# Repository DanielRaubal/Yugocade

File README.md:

<h1 align="center">YugoCade</h1>
<p align="center">Version 0.01</p>

<p align="center">

<p align="center">
Custom handheld arcade system running on Raspberry Pi Pico 2040 MCU, has multiple games on it such as YugoRun, Submarine, Cards, Slot.
</p>

</p>

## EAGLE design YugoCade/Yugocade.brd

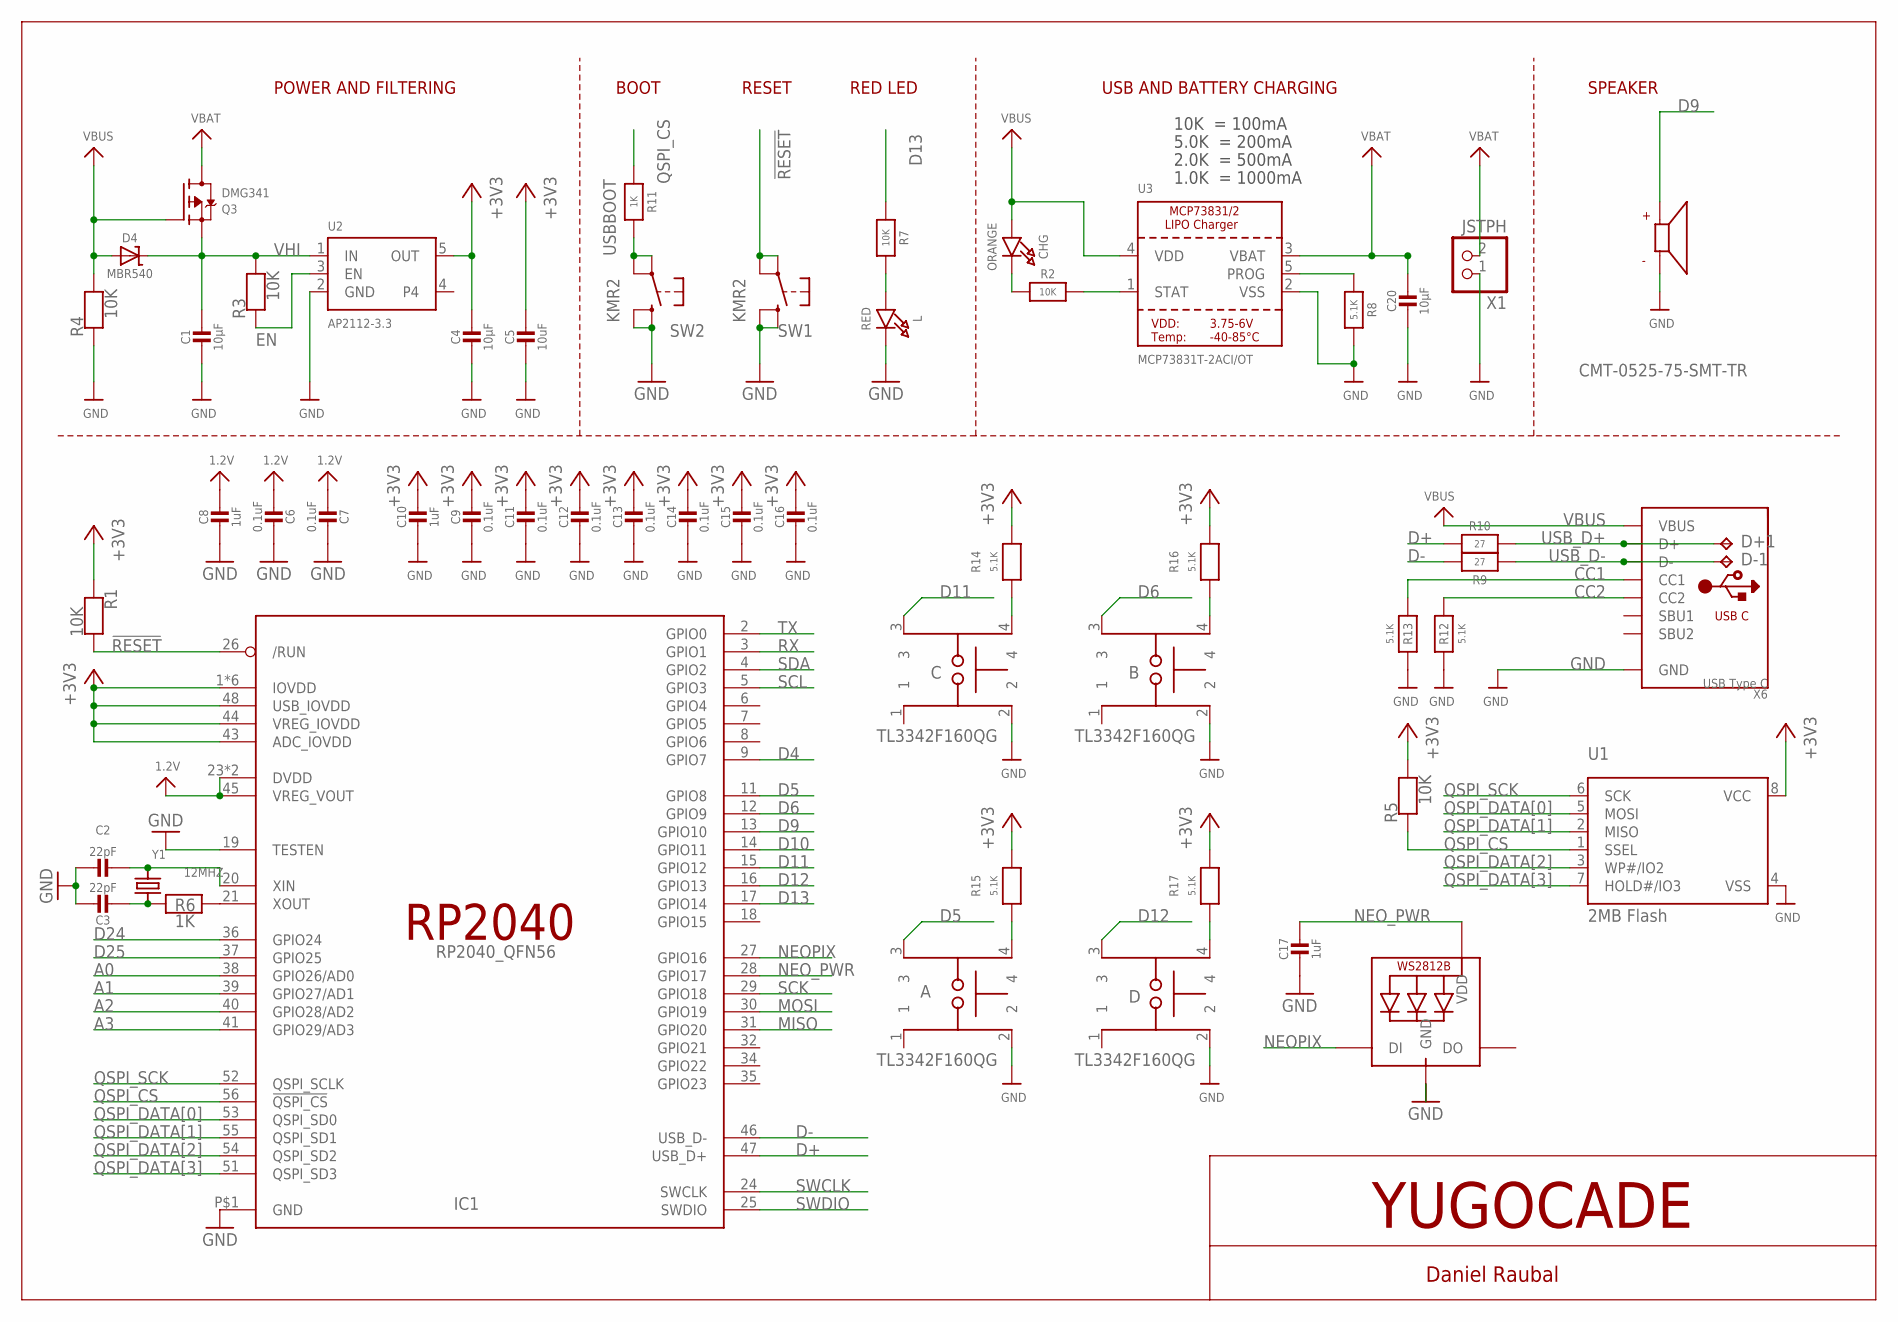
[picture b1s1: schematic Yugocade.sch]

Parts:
A: TL3342F160QG; SW_TL3342F160QG
B: TL3342F160QG; SW_TL3342F160QG
C: TL3342F160QG; SW_TL3342F160QG
C1, C4, C20: 10µF; 0805-NO
C2, C3: 22pF; 0603-NO
C5: 10uF; 0805-NO
C6, C7, C9, C11, C12, C13, C14, C15, C16: 0.1uF; 0603-NO
C8, C10, C17: 1uF; 0603-NO
CHG: ORANGE; CHIPLED_0603_NOOUTLINE
D: TL3342F160QG; SW_TL3342F160QG
D4: MBR540; SOD-123
D+1: TPB1,27; B1,27
D-1: TPB1,27; B1,27
IC1: RP2040_QFN56; QFN56_7MM_REDUCEDEPAD
L: RED; CHIPLED_0603_NOOUTLINE
LED1: WS2812B3535; LED3535
LS1: CMT-0525-75-SMT-TR; XDCR_CMT-0525-75-SMT-TR
Q3: DMG341; SOT23-R
R1, R2, R3, R4, R5, R7: 10K; 0603-NO
R6, R11: 1K; 0603-NO
R8, R12, R13, R14, R15, R16, R17: 5.1K; 0603-NO
R9, R10: 27; 0603-NO
SW1, SW2: KMR2; BTN_KMR2_4.6X2.8
U1: 2MB Flash; SOIC8_208MIL
U2: AP2112-3.3; SOT23-5@1
U3: MCP73831T-2ACI/OT; SOT23-5
X1: JSTPH; JSTPH2_BATT
X6: USB Type C; USB_C_CUSB31-CFM2AX-01-X
Y1: 12MHZ; CRYSTAL_2.5X2

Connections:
1.2V: C6.2, C7.2, C8.1, IC1.23 (DVDD), IC1.45 (VREG_VOUT), IC1.50 (DVDD)
!RESET: IC1.26 (/RUN), R1.2, SW1.A, SW1.A' (P1)
+3V3: C4.1, C5.1, C9.1, C10.1, C11.1, C12.1, C13.1, C14.1, C15.1, C16.1, IC1.1 (IOVDD), IC1.10 (IOVDD), IC1.22 (IOVDD), IC1.33 (IOVDD), IC1.42 (IOVDD), IC1.43 (ADC_IOVDD), IC1.44 (VREG_IOVDD), IC1.48 (USB_IOVDD), IC1.49 (IOVDD), R1.1, R5.2, R14.1, R15.1, R16.1, R17.1, U1.8 (VCC), U2.5 (OUT)
A0: IC1.38 (GPIO26/AD0)
A1: IC1.39 (GPIO27/AD1)
A2: IC1.40 (GPIO28/AD2)
A3: IC1.41 (GPIO29/AD3)
CC1: R13.2, X6.A5 (CC1)
CC2: R12.2, X6.B5 (CC2)
D4: IC1.9 (GPIO7)
D5: A.3, IC1.11 (GPIO8)
D6: B.3, IC1.12 (GPIO9)
D9: IC1.13 (GPIO10), LS1.P
D10: IC1.14 (GPIO11)
D11: C.3, IC1.15 (GPIO12)
D12: D.3, IC1.16 (GPIO13)
D13: IC1.17 (GPIO14), R7.1
D24: IC1.36 (GPIO24)
D25: IC1.37 (GPIO25)
D+: IC1.47 (USB_D+), R10.2
D-: IC1.46 (USB_D-), R9.2
EN: R3.1, U2.3 (EN)
GND: A.2, B.2, C.2, C1.2, C2.1, C3.1, C4.2, C5.2, C6.1, C7.1, C8.2, C9.2, C10.2, C11.2, C12.2, C13.2, C14.2, C15.2, C16.2, C17.2, C20.2, D.2, IC1.19 (TESTEN), IC1.P$1 (GND), L.C, LED1.4 (GND), LS1.N, R4.1, R8.2, R12.1, R13.1, SW1.B (S), SW1.B' (S1), SW2.B (S), SW2.B' (S1), U1.4 (VSS), U2.2 (GND), U3.2 (VSS), X1.1, X6.A1B12 (GND), X6.B1A12 (GND)
MISO: IC1.31 (GPIO20)
MOSI: IC1.30 (GPIO19)
unnamed: CHG.C, R2.1
unnamed: L.A, R7.2
unnamed: R2.2, U3.1 (STAT)
unnamed: R8.1, U3.5 (PROG)
unnamed: C2.2, IC1.20 (XIN), Y1.3 (2)
unnamed: C3.2, R6.1, Y1.1
unnamed: IC1.21 (XOUT), R6.2
unnamed: C.4, R14.2
unnamed: A.4, R15.2
unnamed: B.4, R16.2
unnamed: D.4, R17.2
NEOPIX: IC1.27 (GPIO16), LED1.1 (DI)
NEO_PWR: C17.1, IC1.28 (GPIO17), LED1.2 (VDD)
QSPI_CS: IC1.56 (!QSPI_CS), R5.1, R11.1, U1.1 (SSEL)
QSPI_DATA[0]: IC1.53 (QSPI_SD0), U1.5 (MOSI)
QSPI_DATA[1]: IC1.55 (QSPI_SD1), U1.2 (MISO)
QSPI_DATA[2]: IC1.54 (QSPI_SD2), U1.3 (WP#/IO2)
QSPI_DATA[3]: IC1.51 (QSPI_SD3), U1.7 (HOLD#/IO3)
QSPI_SCK: IC1.52 (QSPI_SCLK), U1.6 (SCK)
RX: IC1.3 (GPIO1)
SCK: IC1.29 (GPIO18)
SCL: IC1.5 (GPIO3)
SDA: IC1.4 (GPIO2)
SWCLK: IC1.24 (SWCLK)
SWDIO: IC1.25 (SWDIO)
TX: IC1.2 (GPIO0)
USBBOOT: R11.2, SW2.A, SW2.A' (P1)
USB_D+: D+1.TP, R10.1, X6.A6 (D+), X6.B6 (D+)
USB_D-: D-1.TP, R9.1, X6.A7 (D-), X6.B7 (D-)
VBAT: C20.1, Q3.3 (D), U3.3 (VBAT), X1.2
VBUS: CHG.A, D4.A, Q3.1 (G), R4.2, U3.4 (VDD), X6.A4B9 (VBUS), X6.B4A9 (VBUS)
VHI: C1.1, D4.C, Q3.2 (S), R3.2, U2.1 (IN)

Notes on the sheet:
POWER AND FILTERING
RESET
10K = 100mA
5.0K = 200mA
2.0K = 500mA
1.0K = 1000mA
USB AND BATTERY CHARGING
RED LED
YUGOCADE
Daniel Raubal
BOOT
SPEAKER

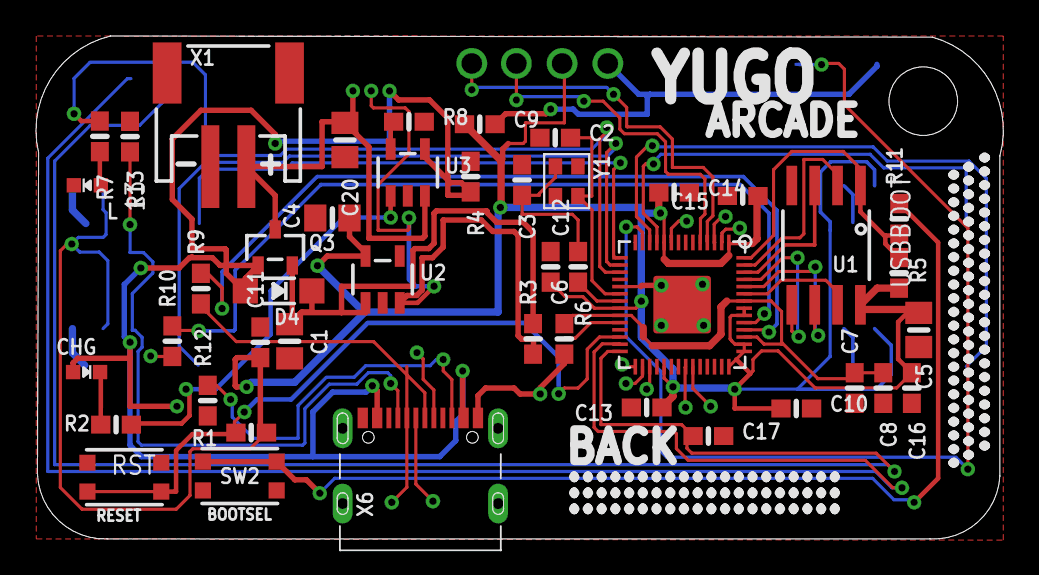
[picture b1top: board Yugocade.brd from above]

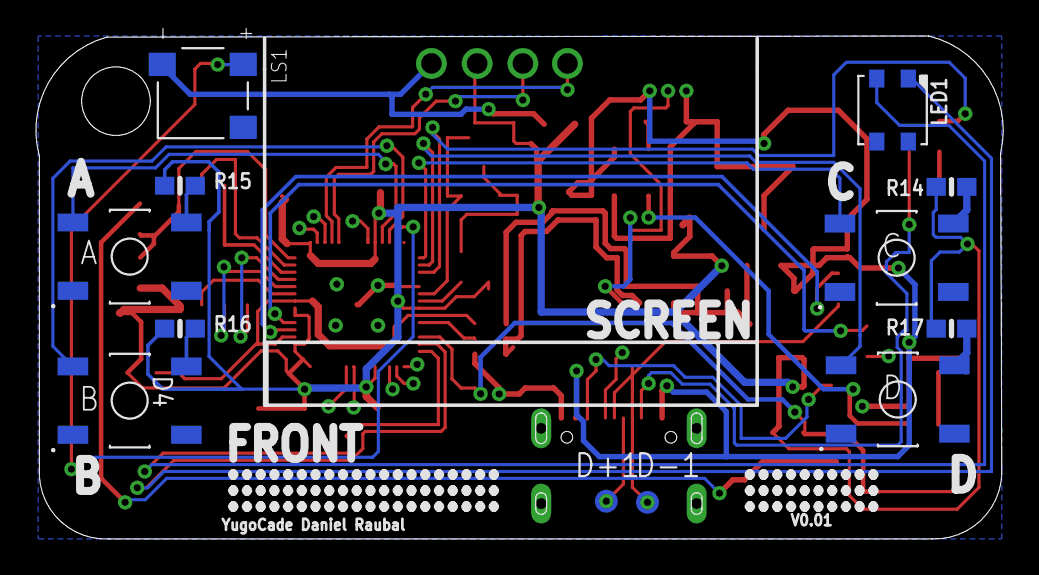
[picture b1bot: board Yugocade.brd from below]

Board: 2 copper layers, 53.7 x 27.9 mm, 56 parts (12 on the bottom side), 40 nets.

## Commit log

2023-05-31 Board, schematic. pdf
2023-06-01 Code
2023-06-01 Image

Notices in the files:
parts and their libraries:
microbuilder: This work is placed in the public domain, and may be freely used for commercial and non-commercial work with the following conditions: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
